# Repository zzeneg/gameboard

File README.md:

# gameboard

Half-keyboard optimized for gaming.

## Features

- 31 regular MX or KS-33/27 switches
- 5-way switch
- 3 push buttons
- per-key LEDs
- 3D printed case

## Photos

## Layout

Optimized for regular WASD setup similar to a normal keyboard, to avoid (or at least minimize) remapping keys for games.

No layer-tap and mod-taps to avoid conflicts (many games require mod presses or holding alpha keys).

1 additional layer to access missing half of keyboard.

Anyway it's easy to change keys on the fly with VIAL.

## Case

Tested on JLCPCB resin printing, it may be a bit tight for FDM.

- [KS-33 Top](./case/top.stl)
- [MX Top](./case/top-mx.stl)
- [Bottom](./case/bottom.stl)
- [5-way knob](./case/5way-short.stl) - lower profile knob, if you want higher profile check out ones from [@sadekbaroudi](https://github.com/sadekbaroudi/fingerpunch/tree/master/3d-models/5-way-tactile-switch-knobs)

## Gerber files

- [PCB](./pcb/production/pcb.zip)

## VIAL firmware

- [source code](https://github.com/zzeneg/vial-qmk/tree/feature/zzeneg/keyboards/gameboard)
- [pre-compiled V1](https://github.com/zzeneg/vial-qmk/releases/download/zzeneg/gameboard_v1_vial.uf2)
- [pre-compiled V2 (with display)](https://github.com/zzeneg/vial-qmk/releases/download/zzeneg/gameboard_v2_vial.uf2)

## Bill of materials

- [PCB](./pcb/production/pcb.zip)
- 3D printed parts (top, bottom, knob)
- Waveshare [RP2040 Zero](https://www.aliexpress.com/item/3256804090654134.html) MCU
- 39 [SMD SOD-123 1N4148](https://www.aliexpress.com/item/1005002882901030.html) diodes
- 1 [5way switch](https://www.aliexpress.com/item/4000681560472.html)
- 3 [push buttons](https://www.aliexpress.com/item/32912263133.html) - default height is 4.3mm but you can use 6-8mm if you want easier access to them
- 31 [RGB LEDs](https://www.aliexpress.com/item/1005003636607308.html)
- [M2 screws with flat head](https://www.aliexpress.com/item/4001248931159.html) - 8mm for MX or 8mm+6mm for KS
- [M2 nuts](https://www.aliexpress.com/item/1005001412230125.html)
- [7x1.5 legs](https://www.aliexpress.com/item/1005002995402961.html)

## Build guide

Please see my [stront guide](https://github.com/zzeneg/stront/blob/main/build-guide/choc/readme.md) for detailed instructions on soldering diodes/LEDs/sockets/MCU.

## MinY version (V2 - ProMicro-compatible, VIK support)

> [!CAUTION]
> This is special version designed for minimal vertical spacing (19x16mm). Regular keycaps will not fit, you must print your own. I prepared several [keycap sets](./case/minY/keycaps/) to choose.
>
> It uses Pro Micro format MCU so it could be wireless (not tested).
>
> I did not make/test case for MX switches - you can modify it in Fusion.

Updated BOM:

- [MCU](https://www.aliexpress.com/item/1005006130019224.html) - ProMicro pinout, bottom pins are needed for I2C and LED only
- [1.47" bare LCD](https://www.aliexpress.com/item/1005004833011998.html) with [VIK adapter](https://github.com/zzeneg/vik-display-adapter) (**PCB <= 1.2mm is recommended**)
- M2 [heatset inserts](https://www.aliexpress.com/item/1005004624377733.html) - 4mm length, 3.2mm diameter for resin case or 3.5mm for Nylon/PLA
- [push buttons](https://www.aliexpress.com/item/1005006143163980.html) - 10mm height for KS, 15mm for MX
- [push button caps](https://www.aliexpress.com/item/1005001584967258.html) - 3.1 inner diameter

## Development

For proper KiCad setup install my [zzkeeb](https://github.com/zzeneg/zzkeeb/blob/main/README.md#installation) library

## Support

If you like my work and want to support my future designs, please consider [sponsorship](https://github.com/sponsors/zzeneg).

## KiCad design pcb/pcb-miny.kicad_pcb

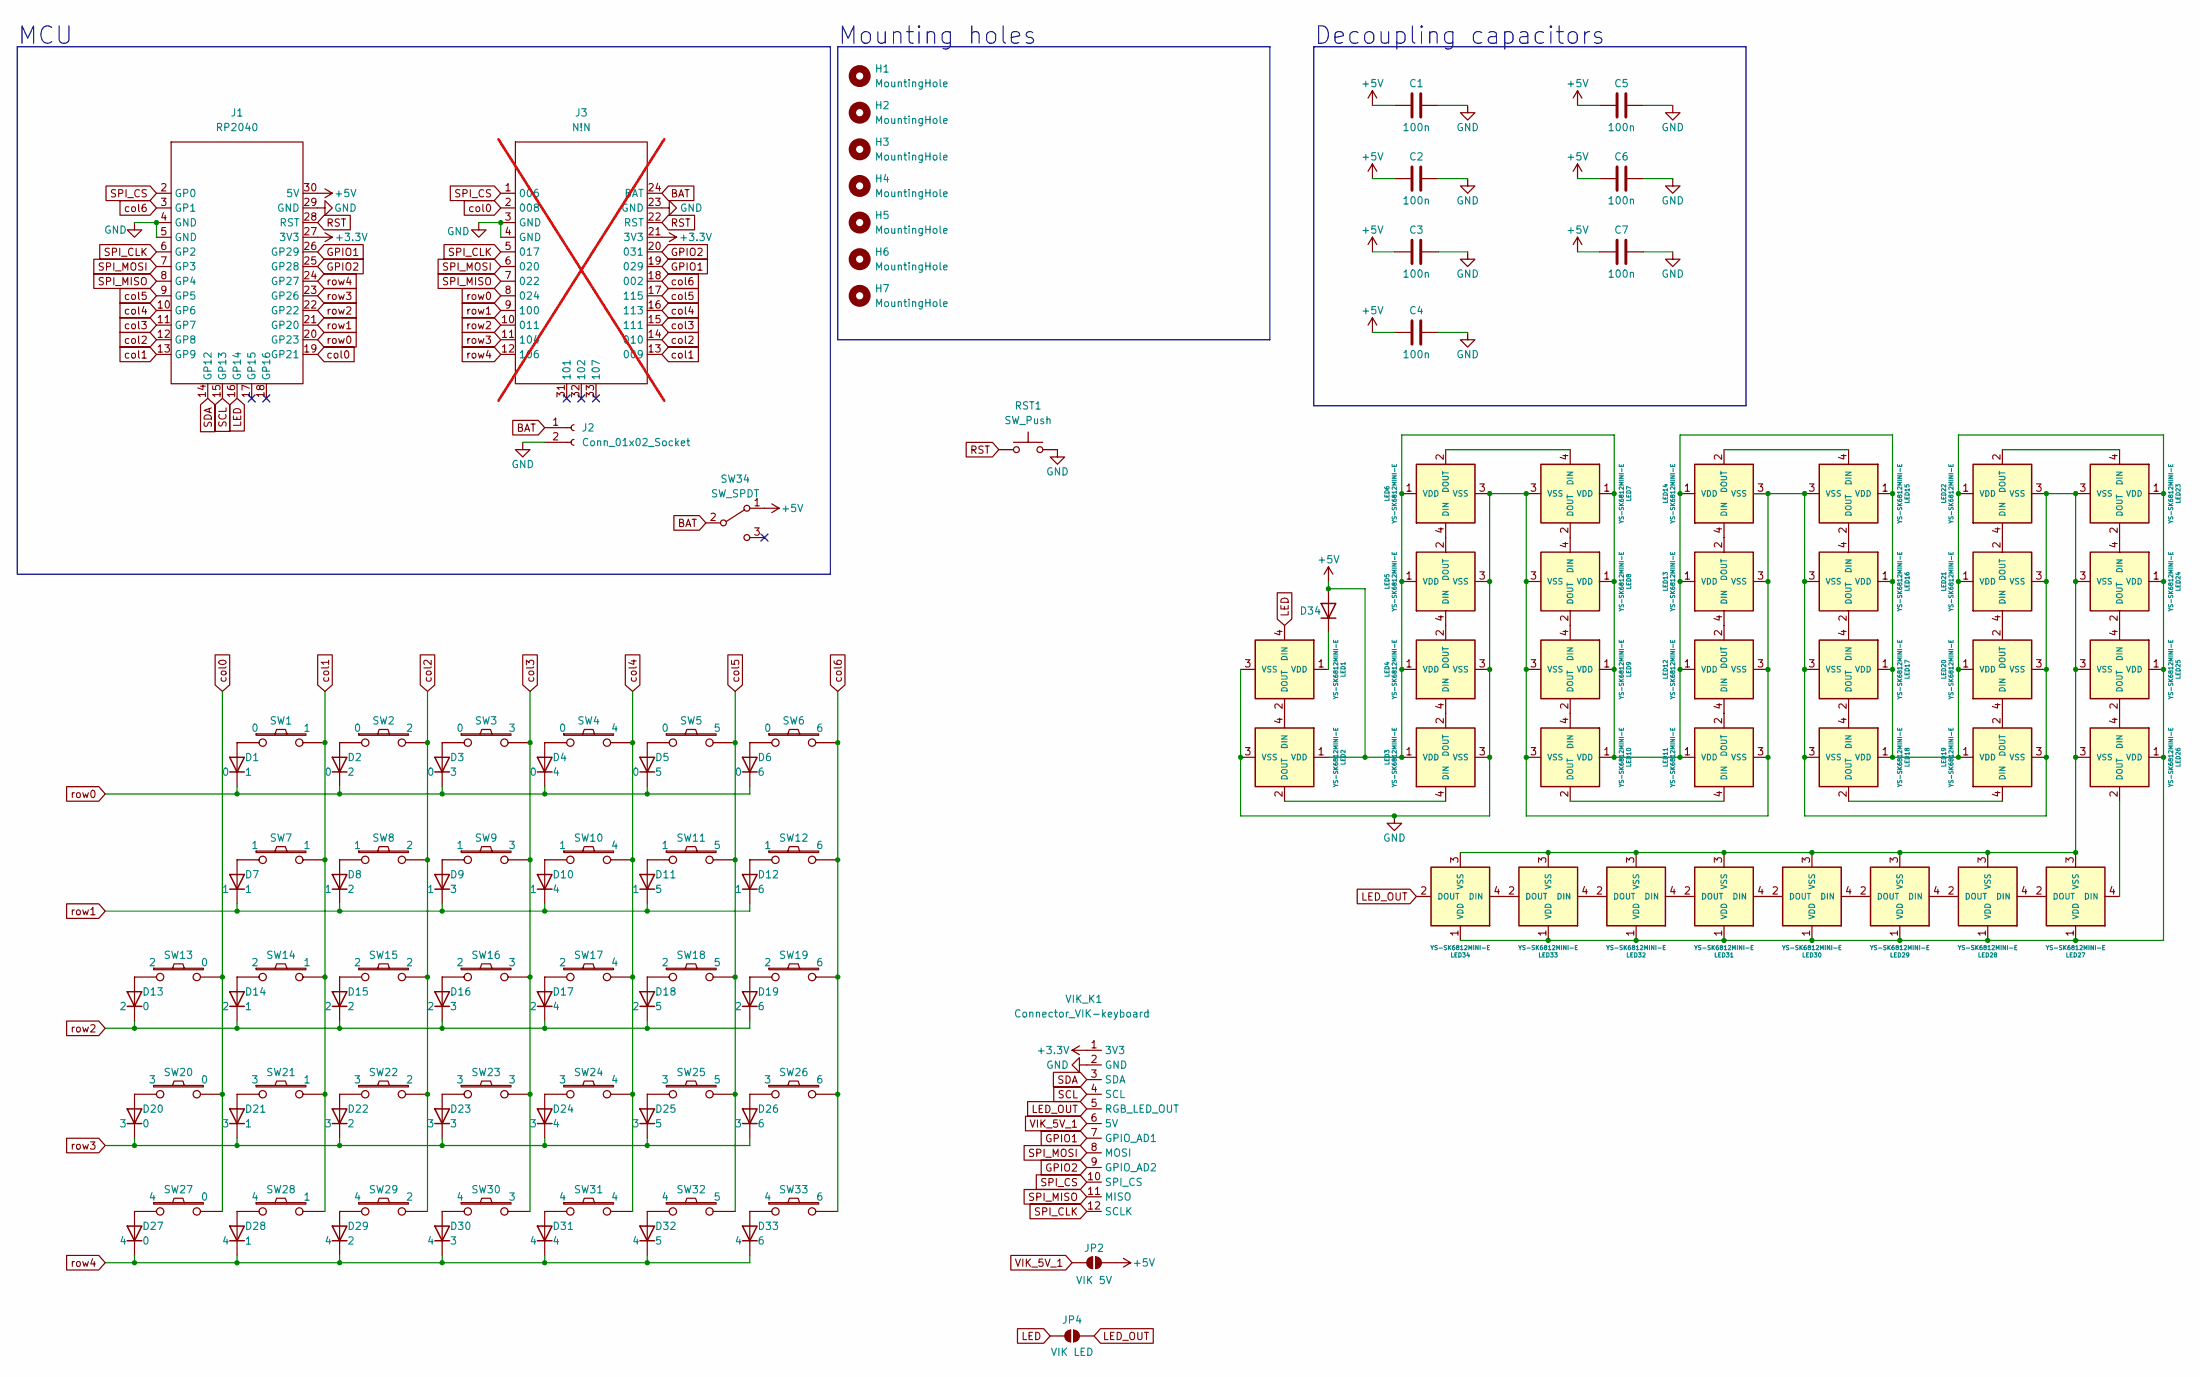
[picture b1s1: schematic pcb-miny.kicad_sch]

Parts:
C1, C2, C3, C4, C5, C6, C7: 100n; C_1206_3216Metric_Pad1.33x1.80mm_HandSolder
D1, D2, D3, D4, D5, D6, D7, D8, D9, D10, D11, D12, D13, D14, D15, D16, D17, D18, D19, D20, D21, D22, D23, D24, D25, D26, D27, D28, D29, D30, D31, D32, D33, D34: D; Diode_1N4148-SOD123
H1, H2, H3, H4, H5, H6, H7: MountingHole; Hole_M2
J1: RP2040; MCU_rp2040-helios
J2: Conn_01x02_Socket; Connector_JST-1x02-2.00mm
J3: N!N; MCU_nice-nano; not fitted
JP2: VIK 5V; SolderJumper-2_P1.3mm_Open_RoundedPad1.0x1.5mm
JP4: VIK LED; SolderJumper-2_P1.3mm_Open_RoundedPad1.0x1.5mm
LED1, LED2, LED3, LED4, LED5, LED6, LED7, LED8, LED9, LED10, LED11, LED12, LED13, LED14, LED15, LED16, LED17, LED18, LED19, LED20, LED21, LED22, LED23, LED24, LED25, LED26, LED27, LED28, LED29, LED30, LED31, LED32, LED33, LED34: YS-SK6812MINI-E; LED_SK6812-MINI-E
RST1: SW_Push; Button_SW_SPST_SKQG_WithoutStem
SW1, SW2, SW3, SW4, SW5, SW6, SW7, SW8, SW9, SW10, SW11, SW12, SW13, SW14, SW15, SW16, SW17, SW18, SW19, SW20, SW21, SW22, SW23, SW24, SW25, SW26, SW30, SW31, SW32, SW33: Switch; Switch_MXKS-miny-hotswap-south-ks3d
SW27, SW28, SW29: Switch; Button_Push-6mm
SW34: SW_SPDT; Switch_SPDT-PCM12
VIK_K1: Connector_VIK-keyboard; Connector_VIK-horizontal-keyboard

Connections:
+3.3V: J1.27 (3V3), J3.21 (3V3), VIK_K1.1 (3V3)
+5V: C1.1, C2.1, C3.1, C4.1, C5.1, C6.1, C7.1, D34.2 (A), J1.30 (5V), JP2.1 (A), LED2.1 (VDD), LED3.1 (VDD), LED4.1 (VDD), LED5.1 (VDD), LED6.1 (VDD), LED7.1 (VDD), LED8.1 (VDD), LED9.1 (VDD), LED10.1 (VDD), LED11.1 (VDD), LED12.1 (VDD), LED13.1 (VDD), LED14.1 (VDD), LED15.1 (VDD), LED16.1 (VDD), LED17.1 (VDD), LED18.1 (VDD), LED19.1 (VDD), LED20.1 (VDD), LED21.1 (VDD), LED22.1 (VDD), LED23.1 (VDD), LED24.1 (VDD), LED25.1 (VDD), LED26.1 (VDD), LED27.1 (VDD), LED28.1 (VDD), LED29.1 (VDD), LED30.1 (VDD), LED31.1 (VDD), LED32.1 (VDD), LED33.1 (VDD), LED34.1 (VDD), SW34.1 (A)
BAT: J2.1, J3.24 (BAT), SW34.2 (B)
GND: C1.2, C2.2, C3.2, C4.2, C5.2, C6.2, C7.2, J1.4 (GND), J1.5 (GND), J1.29 (GND), J2.2, J3.3 (GND), J3.4 (GND), J3.23 (GND), LED1.3 (VSS), LED2.3 (VSS), LED3.3 (VSS), LED4.3 (VSS), LED5.3 (VSS), LED6.3 (VSS), LED7.3 (VSS), LED8.3 (VSS), LED9.3 (VSS), LED10.3 (VSS), LED11.3 (VSS), LED12.3 (VSS), LED13.3 (VSS), LED14.3 (VSS), LED15.3 (VSS), LED16.3 (VSS), LED17.3 (VSS), LED18.3 (VSS), LED19.3 (VSS), LED20.3 (VSS), LED21.3 (VSS), LED22.3 (VSS), LED23.3 (VSS), LED24.3 (VSS), LED25.3 (VSS), LED26.3 (VSS), LED27.3 (VSS), LED28.3 (VSS), LED29.3 (VSS), LED30.3 (VSS), LED31.3 (VSS), LED32.3 (VSS), LED33.3 (VSS), LED34.3 (VSS), RST1.2, VIK_K1.2 (GND)
GPIO1: J1.26 (GP29), J3.19 (029), VIK_K1.7 (GPIO_AD1)
GPIO2: J1.25 (GP28), J3.20 (031), VIK_K1.9 (GPIO_AD2)
LED: J1.16 (GP14), JP4.1 (A), LED1.4 (DIN)
LED_OUT: JP4.2 (B), LED34.2 (DOUT), VIK_K1.5 (RGB_LED_OUT)
unnamed: D1.2 (A), SW1.1
unnamed: D2.2 (A), SW2.1
unnamed: D3.2 (A), SW3.1
unnamed: D4.2 (A), SW4.1
unnamed: D5.2 (A), SW5.1
unnamed: D6.2 (A), SW6.1
unnamed: D7.2 (A), SW7.1
unnamed: D8.2 (A), SW8.1
unnamed: D9.2 (A), SW9.1
unnamed: D10.2 (A), SW10.1
unnamed: D11.2 (A), SW11.1
unnamed: D12.2 (A), SW12.1
unnamed: D13.2 (A), SW13.1
unnamed: D14.2 (A), SW14.1
unnamed: D15.2 (A), SW15.1
unnamed: D16.2 (A), SW16.1
unnamed: D17.2 (A), SW17.1
unnamed: D18.2 (A), SW18.1
unnamed: D19.2 (A), SW19.1
unnamed: D20.2 (A), SW20.1
unnamed: D21.2 (A), SW21.1
unnamed: D22.2 (A), SW22.1
unnamed: D23.2 (A), SW23.1
unnamed: D24.2 (A), SW24.1
unnamed: D25.2 (A), SW25.1
unnamed: D26.2 (A), SW26.1
unnamed: D27.2 (A), SW27.1
unnamed: D28.2 (A), SW28.1
unnamed: D29.2 (A), SW29.1
unnamed: D30.2 (A), SW30.1
unnamed: D31.2 (A), SW31.1
unnamed: D32.2 (A), SW32.1
unnamed: D33.2 (A), SW33.1
unnamed: D34.1 (K), LED1.1 (VDD)
unnamed: LED1.2 (DOUT), LED2.4 (DIN)
unnamed: LED2.2 (DOUT), LED3.4 (DIN)
unnamed: LED3.2 (DOUT), LED4.4 (DIN)
unnamed: LED4.2 (DOUT), LED5.4 (DIN)
unnamed: LED5.2 (DOUT), LED6.4 (DIN)
unnamed: LED6.2 (DOUT), LED7.4 (DIN)
unnamed: LED7.2 (DOUT), LED8.4 (DIN)
unnamed: LED8.2 (DOUT), LED9.4 (DIN)
unnamed: LED9.2 (DOUT), LED10.4 (DIN)
unnamed: LED10.2 (DOUT), LED11.4 (DIN)
unnamed: LED11.2 (DOUT), LED12.4 (DIN)
unnamed: LED12.2 (DOUT), LED13.4 (DIN)
unnamed: LED13.2 (DOUT), LED14.4 (DIN)
unnamed: LED14.2 (DOUT), LED15.4 (DIN)
unnamed: LED15.2 (DOUT), LED16.4 (DIN)
unnamed: LED16.2 (DOUT), LED17.4 (DIN)
unnamed: LED17.2 (DOUT), LED18.4 (DIN)
unnamed: LED18.2 (DOUT), LED19.4 (DIN)
unnamed: LED19.2 (DOUT), LED20.4 (DIN)
unnamed: LED20.2 (DOUT), LED21.4 (DIN)
unnamed: LED21.2 (DOUT), LED22.4 (DIN)
unnamed: LED22.2 (DOUT), LED23.4 (DIN)
unnamed: LED23.2 (DOUT), LED24.4 (DIN)
unnamed: LED24.2 (DOUT), LED25.4 (DIN)
unnamed: LED25.2 (DOUT), LED26.4 (DIN)
unnamed: LED26.2 (DOUT), LED27.4 (DIN)
unnamed: LED27.2 (DOUT), LED28.4 (DIN)
unnamed: LED28.2 (DOUT), LED29.4 (DIN)
unnamed: LED29.2 (DOUT), LED30.4 (DIN)
unnamed: LED30.2 (DOUT), LED31.4 (DIN)
unnamed: LED31.2 (DOUT), LED32.4 (DIN)
unnamed: LED32.2 (DOUT), LED33.4 (DIN)
unnamed: LED33.2 (DOUT), LED34.4 (DIN)
RST: J1.28 (RST), J3.22 (RST), RST1.1
SCL: J1.15 (GP13), VIK_K1.4 (SCL)
SDA: J1.14 (GP12), VIK_K1.3 (SDA)
SPI_CLK: J1.6 (GP2), J3.5 (017), VIK_K1.12 (SCLK)
SPI_CS: J1.2 (GP0), J3.1 (006), VIK_K1.10 (SPI_CS)
SPI_MISO: J1.8 (GP4), J3.7 (022), VIK_K1.11 (MISO)
SPI_MOSI: J1.7 (GP3), J3.6 (020), VIK_K1.8 (MOSI)
VIK_5V_1: JP2.2 (B), VIK_K1.6 (5V)
col0: J1.19 (GP21), J3.2 (008), SW13.2, SW20.2, SW27.2
col1: J1.13 (GP9), J3.13 (009), SW1.2, SW7.2, SW14.2, SW21.2, SW28.2
col2: J1.12 (GP8), J3.14 (010), SW2.2, SW8.2, SW15.2, SW22.2, SW29.2
col3: J1.11 (GP7), J3.15 (111), SW3.2, SW9.2, SW16.2, SW23.2, SW30.2
col4: J1.10 (GP6), J3.16 (113), SW4.2, SW10.2, SW17.2, SW24.2, SW31.2
col5: J1.9 (GP5), J3.17 (115), SW5.2, SW11.2, SW18.2, SW25.2, SW32.2
col6: J1.3 (GP1), J3.18 (002), SW6.2, SW12.2, SW19.2, SW26.2, SW33.2
row0: D1.1 (K), D2.1 (K), D3.1 (K), D4.1 (K), D5.1 (K), D6.1 (K), J1.20 (GP23), J3.8 (024)
row1: D7.1 (K), D8.1 (K), D9.1 (K), D10.1 (K), D11.1 (K), D12.1 (K), J1.21 (GP20), J3.9 (100)
row2: D13.1 (K), D14.1 (K), D15.1 (K), D16.1 (K), D17.1 (K), D18.1 (K), D19.1 (K), J1.22 (GP22), J3.10 (011)
row3: D20.1 (K), D21.1 (K), D22.1 (K), D23.1 (K), D24.1 (K), D25.1 (K), D26.1 (K), J1.23 (GP26), J3.11 (104)
row4: D27.1 (K), D28.1 (K), D29.1 (K), D30.1 (K), D31.1 (K), D32.1 (K), D33.1 (K), J1.24 (GP27), J3.12 (106)

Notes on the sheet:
Decoupling capacitors
Mounting holes
MCU

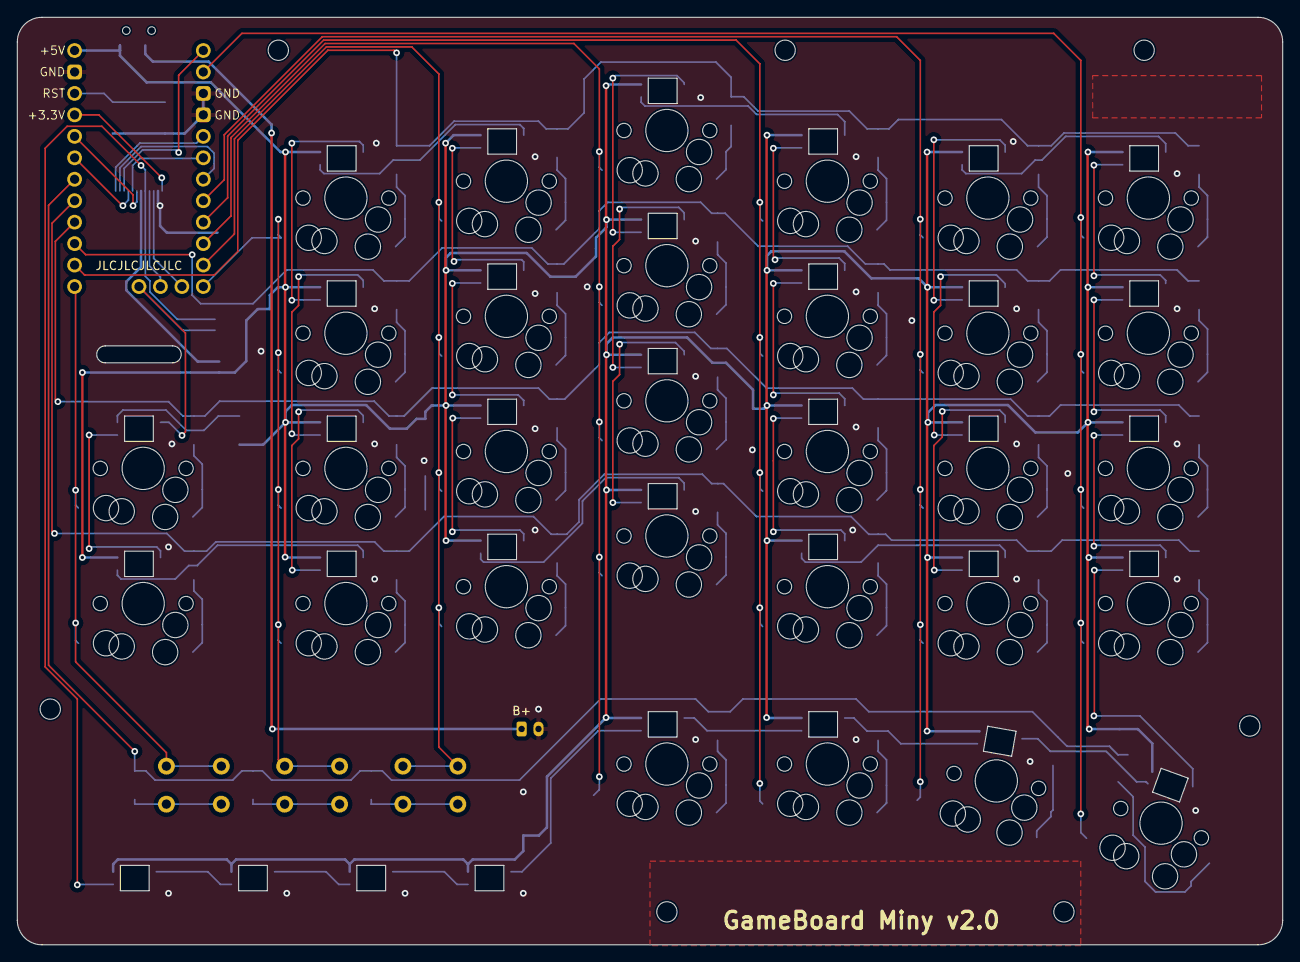
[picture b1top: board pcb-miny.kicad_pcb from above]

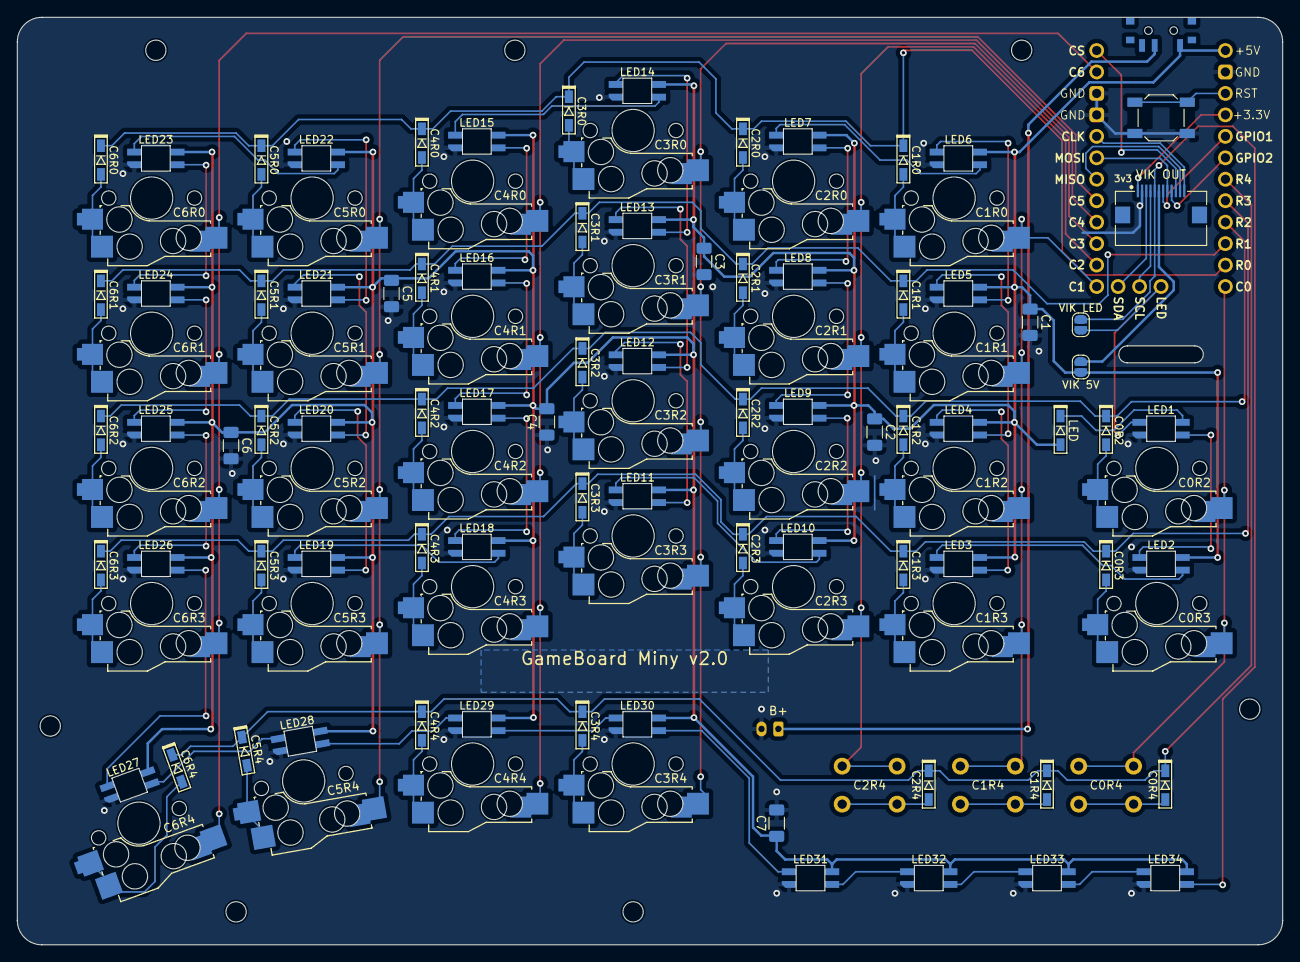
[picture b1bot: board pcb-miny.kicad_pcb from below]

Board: 2 copper layers, 149.8 x 109.8 mm, 122 parts (81 on the bottom side), 95 nets.

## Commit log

2023-08-19 add pcb
2023-08-19 pcb updates
2023-08-19 add case
2023-09-01 PCB 1.1
2023-09-02 update case
2023-09-03 add readme
2023-11-20 add MX case
2024-01-10 add miny
2024-01-13 add TPU case
2024-01-13 add CMY keycaps
2024-01-13 add decoupling capacitors
2024-02-04 update tpu case, add mx
2024-02-04 remove miny case (not tested)
2024-02-04 fix KS case after updates
2024-02-16 add DES keycaps
2024-02-19 fix keycaps
2024-04-15 restructure project
2024-04-15 restructure
2024-04-21 add minY-minZ keycaps
2024-04-21 small minY case updates
2024-05-02 miny-v2 draft
2024-05-03 fix chamfer
2024-05-03 small pcb updates, rounded
2024-05-26 fix rounded pcb
2024-05-30 add more screw holes, remove rounded pcb
2024-05-30 update minY case
2024-06-26 final case and pcb
2024-06-28 remove minY v1
2025-01-16 update des keycaps
